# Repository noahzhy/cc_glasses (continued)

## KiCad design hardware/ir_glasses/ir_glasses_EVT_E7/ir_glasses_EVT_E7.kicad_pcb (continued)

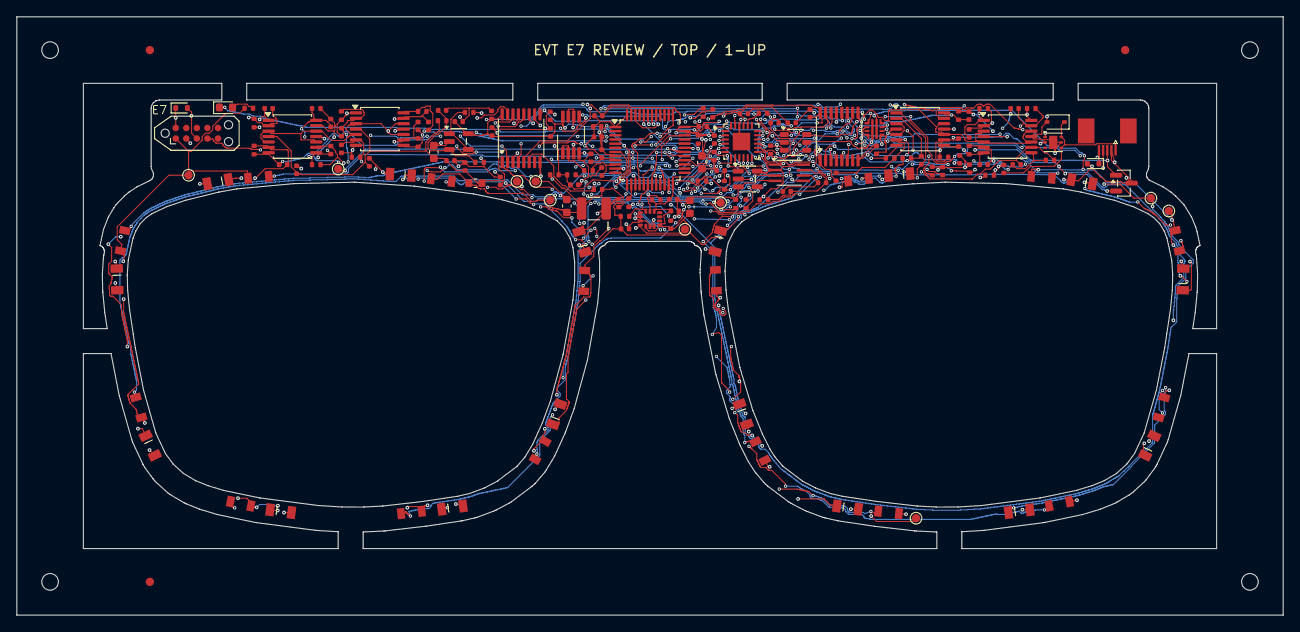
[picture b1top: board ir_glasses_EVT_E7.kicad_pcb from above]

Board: 4 copper layers, 152.3 x 72.0 mm, 171 parts (0 on the bottom side), 97 nets.

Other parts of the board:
FID1, FID2, FID3: Fiducial_1mm_Mask2mm
H1, H2, H3, H4: MountingHole_2mm

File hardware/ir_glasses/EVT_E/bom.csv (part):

Reference,Value,Footprint,Quantity,Populate,X_mm,Y_mm,Rotation_deg,Side
U9,STM32C031C6T6,IR_Glasses:LQFP-48_7x7mm_P0.5mm,1,Yes,110,63,0,front
U1,TLC59283RGER,IR_Glasses:Texas_RGE0024C_VQFN-24-1EP_4x4mm_P0.5mm_EP2.1x2.1mm,1,Yes,121,62,0,front
U10,LSM6DS3TR-C,IR_Glasses:LGA-14_3x2.5mm_P0.5mm_LayoutBorder3x4y,1,Yes,110,71.3,0,front
U6,TLV9061IDBVR,IR_Glasses:SOT-23-5,1,Yes,87,62,0,front
J1,TE 0-1734839-5,IR_Glasses:TE_0-1734839-5_1x05-1MP_P0.5mm_Horizontal,1,Yes,165,61.7,180,front
J2,TC2050-IDC-NL / ARM2010,IR_Glasses:Tag-Connect_TC2050-IDC-NL_2x05_P1.27mm_Vertical,1,PCB pads only,55.5,61,0,front
U11,PESD3V3L2BT,IR_Glasses:SOT-23,1,Yes,167.5,67.0,0,front
D17,PESD3V3S1BA,IR_Glasses:D_SOD-323,1,Yes,159.0,60.0,90,front
FB1,600R@100MHz 500mA,IR_Glasses:L_0603_1608Metric,1,Yes,89.0,67.0,0,front
NT1,AGND-GND star,IR_Glasses:NetTie-2_SMD_Pad0.5mm,1,PCB pads only,92.0,67.0,0,front
R1,2.65k,IR_Glasses:R_0402_1005Metric,1,Yes,125.75,63.25,90,front
R2,10k,IR_Glasses:R_0402_1005Metric,1,Yes,85.0,59.5,0,front
R3,10k,IR_Glasses:R_0402_1005Metric,1,Yes,86.0,64.5,0,front
R4,10k,IR_Glasses:R_0402_1005Metric,1,Yes,103.5,61.0,0,front
R5,100k,IR_Glasses:R_0402_1005Metric,1,Yes,115.8,61.0,90,front
R6,4.7k,IR_Glasses:R_0402_1005Metric,1,Yes,113.0,70.0,0,front
R7,4.7k,IR_Glasses:R_0402_1005Metric,1,Yes,113.5,72.0,90,front
R8,22,IR_Glasses:R_0402_1005Metric,1,Yes,154.0,66.0,0,front
R9,22,IR_Glasses:R_0402_1005Metric,1,Yes,170.0,69.5,0,front
R10,10k,IR_Glasses:R_0402_1005Metric,1,Yes,125.75,60.0,90,front
R11,100,IR_Glasses:R_0402_1005Metric,1,Yes,102.0,67.0,0,front
R12,100,IR_Glasses:R_0402_1005Metric,1,Yes,116.0,67.0,90,front
R13,47,IR_Glasses:R_0402_1005Metric,1,Yes,89.75,60.0,90,front
U2,TLV9064IPWR,IR_Glasses:TSSOP-14_4.4x5mm_P0.65mm,1,Yes,77.5,60.5,0,front
U3,TLV9064IPWR,IR_Glasses:TSSOP-14_4.4x5mm_P0.65mm,1,Yes,67,61.4,0,front
PD1,PD15-22B/TR8,IR_Glasses:Everlight_PD15_22B,1,Yes,99.1474,94.9322,69.734,front
D1,IR11-21C/TR8,IR_Glasses:Everlight_IR11_21C,1,Yes,97.2266,99.389,61.38,front
RF1,100k,IR_Glasses:R_0402_1005Metric,1,Yes,72.888,58.875,90,front
CF1,22p C0G,IR_Glasses:C_0402_1005Metric,1,Yes,72.888,60.875,90,front
PD2,PD15-22B/TR8,IR_Glasses:Everlight_PD15_22B,1,Yes,86.2915,106.4166,9.481,front
D2,IR11-21C/TR8,IR_Glasses:Everlight_IR11_21C,1,Yes,81.3647,107.0997,6.53,front
RF2,100k,IR_Glasses:R_0402_1005Metric,1,Yes,74.638,63.875,0,front
CF2,22p C0G,IR_Glasses:C_0402_1005Metric,1,Yes,72.888,62.875,90,front
PD3,PD15-22B/TR8,IR_Glasses:Everlight_PD15_22B,1,Yes,65.5404,106.8475,-7.387,front
D3,IR11-21C/TR8,IR_Glasses:Everlight_IR11_21C,1,Yes,60.667,106.0473,-11.779,front
RF3,100k,IR_Glasses:R_0402_1005Metric,1,Yes,82.112,62.125,90,front
CF3,22p C0G,IR_Glasses:C_0402_1005Metric,1,Yes,82.112,60.125,90,front
PD4,PD15-22B/TR8,IR_Glasses:Everlight_PD15_22B,1,Yes,49.5328,98.7372,-65.946,front
D4,IR11-21C/TR8,IR_Glasses:Everlight_IR11_21C,1,Yes,48.0093,94.1124,-74.093,front
RF4,100k,IR_Glasses:R_0402_1005Metric,1,Yes,82.612,58.375,0,front
CF4,22p C0G,IR_Glasses:C_0402_1005Metric,1,Yes,83.362,60.125,90,front
PD5,PD15-22B/TR8,IR_Glasses:Everlight_PD15_22B,1,Yes,45.494200000000006,78.5897,-89.524,front
D5,IR11-21C/TR8,IR_Glasses:Everlight_IR11_21C,1,Yes,46.0878,73.8218,-105.15,front
RF5,100k,IR_Glasses:R_0402_1005Metric,1,Yes,62.388,59.775,90,front
CF5,22p C0G,IR_Glasses:C_0402_1005Metric,1,Yes,64.138,58.025,0,front
PD6,PD15-22B/TR8,IR_Glasses:Everlight_PD15_22B,1,Yes,57.9682,66.4324,-167.812,front
D6,IR11-21C/TR8,IR_Glasses:Everlight_IR11_21C,1,Yes,62.8597,65.8002,-174.743,front
RF6,100k,IR_Glasses:R_0402_1005Metric,1,Yes,62.388,63.025,90,front
CF6,22p C0G,IR_Glasses:C_0402_1005Metric,1,Yes,65.888,64.775,0,front
PD7,PD15-22B/TR8,IR_Glasses:Everlight_PD15_22B,1,Yes,80.0574,65.60249999999999,176.212,front
D7,IR11-21C/TR8,IR_Glasses:Everlight_IR11_21C,1,Yes,84.9772,66.1358,172.509,front
RF7,100k,IR_Glasses:R_0402_1005Metric,1,Yes,69.862,64.775,0,front
CF7,22p C0G,IR_Glasses:C_0402_1005Metric,1,Yes,71.612,63.025,90,front
PD8,PD15-22B/TR8,IR_Glasses:Everlight_PD15_22B,1,Yes,102.2158,73.9515,106.619,front
D8,IR11-21C/TR8,IR_Glasses:Everlight_IR11_21C,1,Yes,102.5903,78.7863,87.338,front
RF8,100k,IR_Glasses:R_0402_1005Metric,1,Yes,69.862,58.025,0,front
CF8,22p C0G,IR_Glasses:C_0402_1005Metric,1,Yes,71.612,59.775,90,front
U7,TMUX1308PWR,IR_Glasses:TSSOP-16_4.4x5mm_P0.65mm,1,Yes,95,62,0,front
U4,TLV9064IPWR,IR_Glasses:TSSOP-14_4.4x5mm_P0.65mm,1,Yes,142.5,60.5,0,front
U5,TLV9064IPWR,IR_Glasses:TSSOP-14_4.4x5mm_P0.65mm,1,Yes,153,61.4,0,front
PD9,PD15-22B/TR8,IR_Glasses:Everlight_PD15_22B,1,Yes,120.8321,94.9333,-70.297,front
D9,IR11-21C/TR8,IR_Glasses:Everlight_IR11_21C,1,Yes,122.806,99.4398,-61.268,front
RF9,100k,IR_Glasses:R_0402_1005Metric,1,Yes,137.888,58.875,90,front
CF9,22p C0G,IR_Glasses:C_0402_1005Metric,1,Yes,137.888,60.875,90,front
PD10,PD15-22B/TR8,IR_Glasses:Everlight_PD15_22B,1,Yes,133.70850000000002,106.4166,-9.481,front
D10,IR11-21C/TR8,IR_Glasses:Everlight_IR11_21C,1,Yes,138.6353,107.0997,-6.53,front
RF10,100k,IR_Glasses:R_0402_1005Metric,1,Yes,137.888,62.875,90,front
CF10,22p C0G,IR_Glasses:C_0402_1005Metric,1,Yes,136.638,62.125,90,front
PD11,PD15-22B/TR8,IR_Glasses:Everlight_PD15_22B,1,Yes,154.4596,106.8475,7.387,front
D11,IR11-21C/TR8,IR_Glasses:Everlight_IR11_21C,1,Yes,159.333,106.0473,11.779,front
RF11,100k,IR_Glasses:R_0402_1005Metric,1,Yes,145.362,63.875,0,front
CF11,22p C0G,IR_Glasses:C_0402_1005Metric,1,Yes,147.112,62.125,90,front
PD12,PD15-22B/TR8,IR_Glasses:Everlight_PD15_22B,1,Yes,170.4672,98.7372,65.946,front
D12,IR11-21C/TR8,IR_Glasses:Everlight_IR11_21C,1,Yes,171.9907,94.1124,74.093,front
RF12,100k,IR_Glasses:R_0402_1005Metric,1,Yes,147.112,58.875,90,front
CF12,22p C0G,IR_Glasses:C_0402_1005Metric,1,Yes,148.362,58.875,90,front
PD13,PD15-22B/TR8,IR_Glasses:Everlight_PD15_22B,1,Yes,174.5058,78.5897,89.524,front
D13,IR11-21C/TR8,IR_Glasses:Everlight_IR11_21C,1,Yes,173.91219999999998,73.8218,105.15,front
RF13,100k,IR_Glasses:R_0402_1005Metric,1,Yes,150.138,58.025,0,front
CF13,22p C0G,IR_Glasses:C_0402_1005Metric,1,Yes,148.388,61.025,90,front
PD14,PD15-22B/TR8,IR_Glasses:Everlight_PD15_22B,1,Yes,162.0318,66.4324,167.812,front
D14,IR11-21C/TR8,IR_Glasses:Everlight_IR11_21C,1,Yes,157.1403,65.8002,174.743,front
RF14,100k,IR_Glasses:R_0402_1005Metric,1,Yes,148.388,63.025,90,front
CF14,22p C0G,IR_Glasses:C_0402_1005Metric,1,Yes,150.138,64.775,0,front
PD15,PD15-22B/TR8,IR_Glasses:Everlight_PD15_22B,1,Yes,139.9583,65.5798,-174.859,front
D15,IR11-21C/TR8,IR_Glasses:Everlight_IR11_21C,1,Yes,135.00979999999998,66.0825,-173.002,front
RF15,100k,IR_Glasses:R_0402_1005Metric,1,Yes,158.112,64.025,0,front
CF15,22p C0G,IR_Glasses:C_0402_1005Metric,1,Yes,154.112,64.775,0,front
PD16,PD15-22B/TR8,IR_Glasses:Everlight_PD15_22B,1,Yes,117.7834,73.8917,-106.197,front
D16,IR11-21C/TR8,IR_Glasses:Everlight_IR11_21C,1,Yes,117.4309,78.7127,-87.24,front
RF16,100k,IR_Glasses:R_0402_1005Metric,1,Yes,155.862,58.025,0,front
CF16,22p C0G,IR_Glasses:C_0402_1005Metric,1,Yes,153.862,58.025,0,front
U8,TMUX1308PWR,IR_Glasses:TSSOP-16_4.4x5mm_P0.65mm,1,Yes,131,61.5,0,front
C1,1u,IR_Glasses:C_0402_1005Metric,1,Yes,85.0,58.25,0,front
C2,100n,IR_Glasses:C_0402_1005Metric,1,Yes,121.25,58.562,0,front
C3,100n,IR_Glasses:C_0402_1005Metric,1,Yes,76.388,64.5,90,front
C4,100n,IR_Glasses:C_0402_1005Metric,1,Yes,61.888,58.15,0,front
C5,100n,IR_Glasses:C_0402_1005Metric,1,Yes,136.638,60.0,90,front
C6,100n,IR_Glasses:C_0402_1005Metric,1,Yes,147.888,64.65,0,front
C7,100n,IR_Glasses:C_0402_1005Metric,1,Yes,88.138,59.55,0,front
C8,100n,IR_Glasses:C_0402_1005Metric,1,Yes,97.862,58.475,0,front
C9,100n,IR_Glasses:C_0402_1005Metric,1,Yes,133.862,57.975,0,front
C10,100n,IR_Glasses:C_0402_1005Metric,1,Yes,112.75,68.913,0,front
C11,100n,IR_Glasses:C_0402_1005Metric,1,Yes,104.088,64.25,90,front
C12,100n,IR_Glasses:C_0402_1005Metric,1,Yes,112.412,72.05,90,front
C13,100n,IR_Glasses:C_0402_1005Metric,1,Yes,107.5,72.212,90,front
C14,100n,IR_Glasses:C_0402_1005Metric,1,Yes,170.5,68.05,0,front
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
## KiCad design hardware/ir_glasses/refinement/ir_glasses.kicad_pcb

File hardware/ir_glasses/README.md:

# IR Glasses EVT E6

当前修复后的设计为 **EVT E6 P3**：每颗 IR LED 同步读取相邻两个 PD，16 组固定配对。E4 原工程、原 BOM 和生产包保留。

- [E6 工程及交付说明](ir_glasses_EVT_E6/README.md)
- [P3 运放替代与模拟验证](ir_glasses_EVT_E6/analog_validation_report.md)
- [P2 完善与复核报告](ir_glasses_EVT_E6/production_refinement_report.md)
- [P1 历史修复记录](ir_glasses_EVT_E6/production_fix_report.md)
- [完整 E6 工程包](ir_glasses_EVT_E6.zip)
- [载框 Gerber 上传包](ir_glasses_EVT_E6_JLC_upload.zip)
- [贴片交付包](ir_glasses_EVT_E6/EVT_E6_SMT_handoff.zip)
- [贴好片示意图](ir_glasses_EVT_E6/populated_assembly.pdf)
- [E6 BOM](ir_glasses_EVT_E6/bom_EVT_E6.xlsx)

主板及载框 DRC、ERC、原理图一致性、CAM/BOM/CPL 静态检查已通过。正常输入要求 3.3V±3%，板上新增持续限流和过压恢复保护。工厂 DFM、备料、实际排线和首板电气/光学/固件验证仍待完成；本包不含可烧录固件，不能把静态检查视为量产实测放行。

## E4 基线与历史证据

- [E4 KiCad 工程](ir_glasses_EVT_E4/ir_glasses_EVT_E4.kicad_pro)
- [E4 完整交付包](ir_glasses_EVT_E4.zip)
- [E4 上传包](ir_glasses_EVT_E4_JLC_upload.zip)
- [E4 BOM](ir_glasses_EVT_E4/material_freeze/bom.xlsx)
- [本次修复前复核记录](EVT_E6_preproduction_audit/REVIEW.md)

E6 BOM 以两板净用量作参考，不含贴片损耗、最小起订量及备件；实际生产数量另行确定。

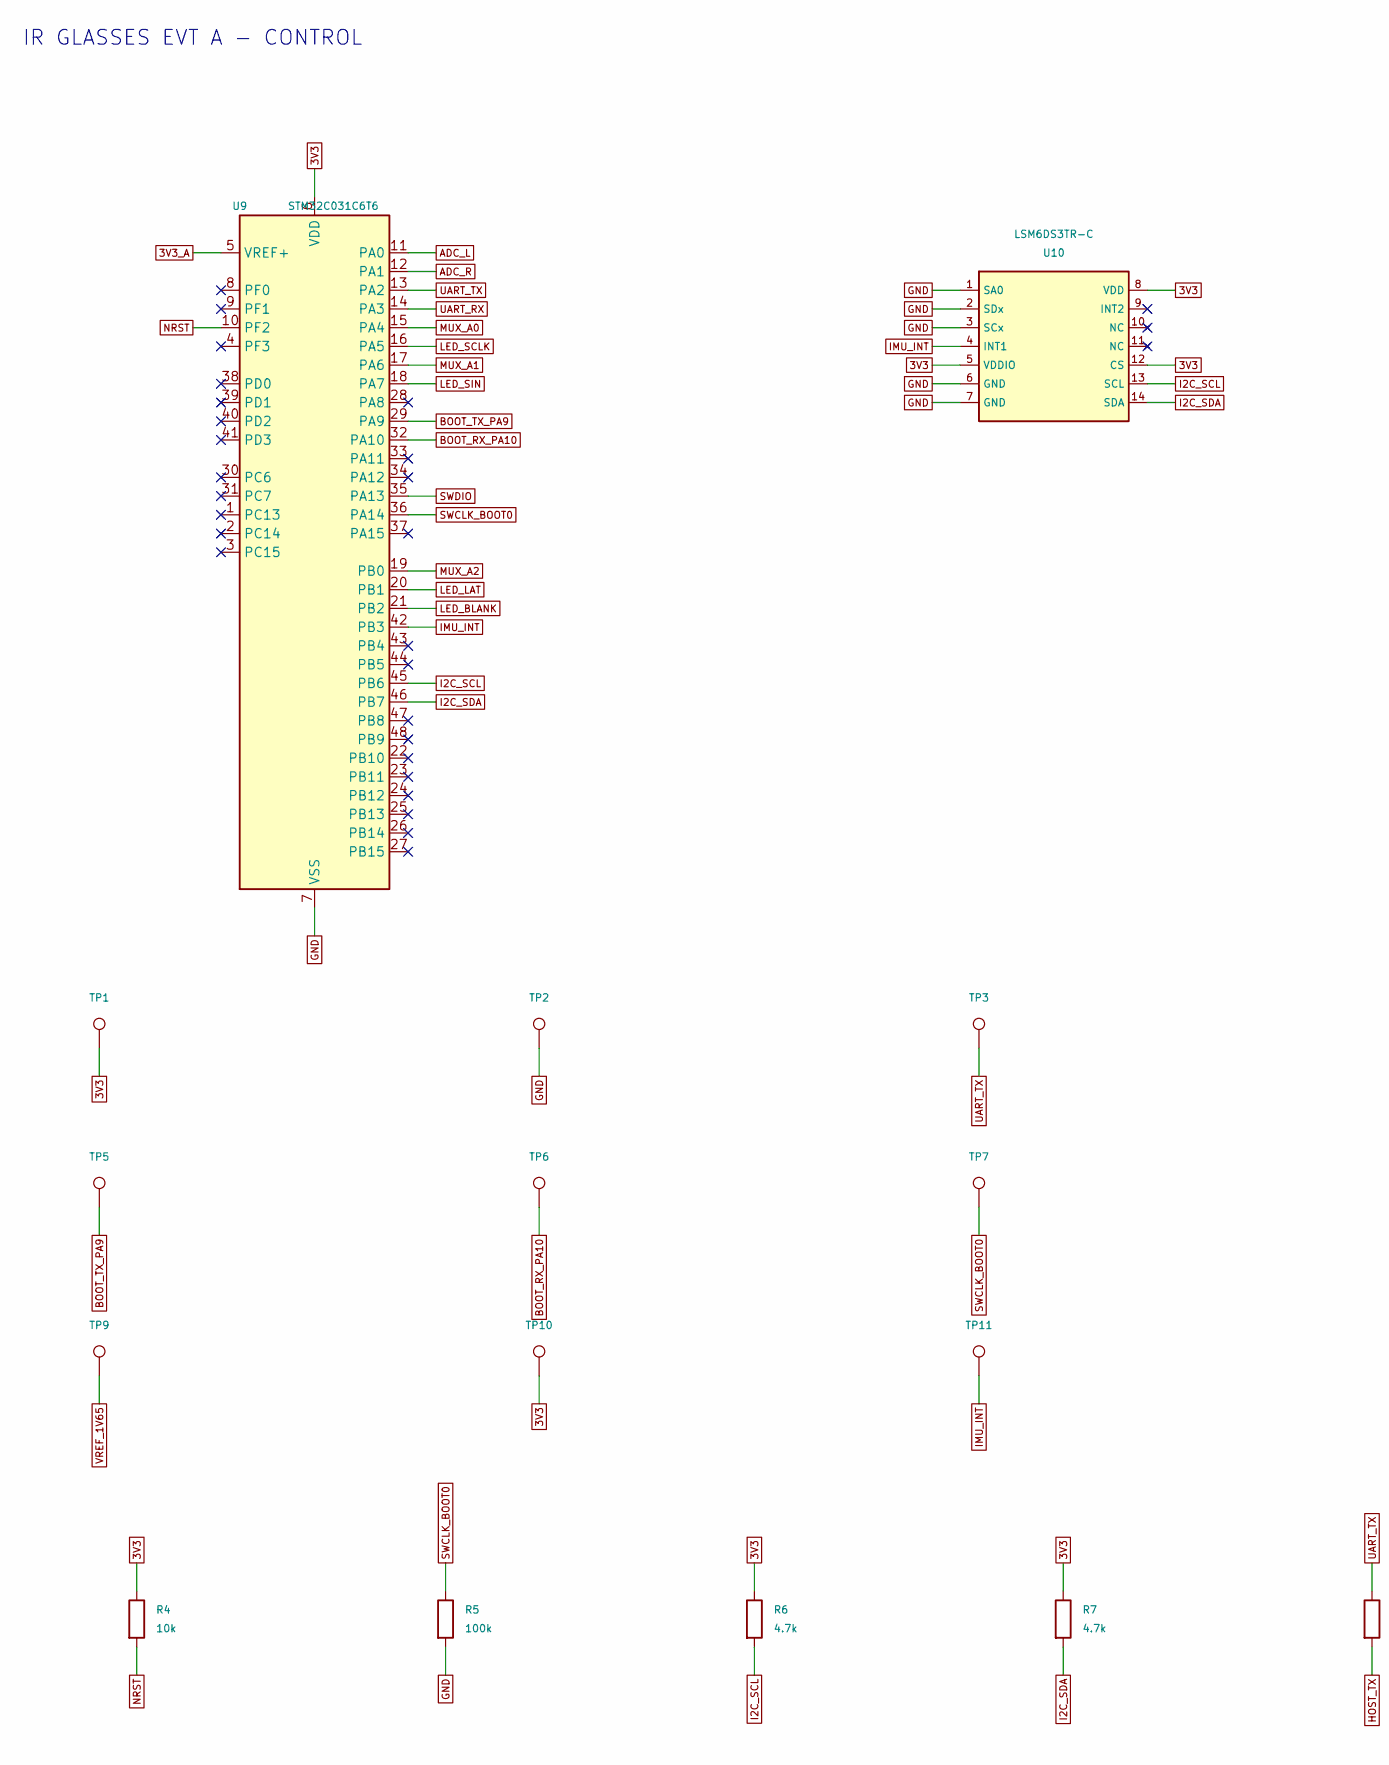
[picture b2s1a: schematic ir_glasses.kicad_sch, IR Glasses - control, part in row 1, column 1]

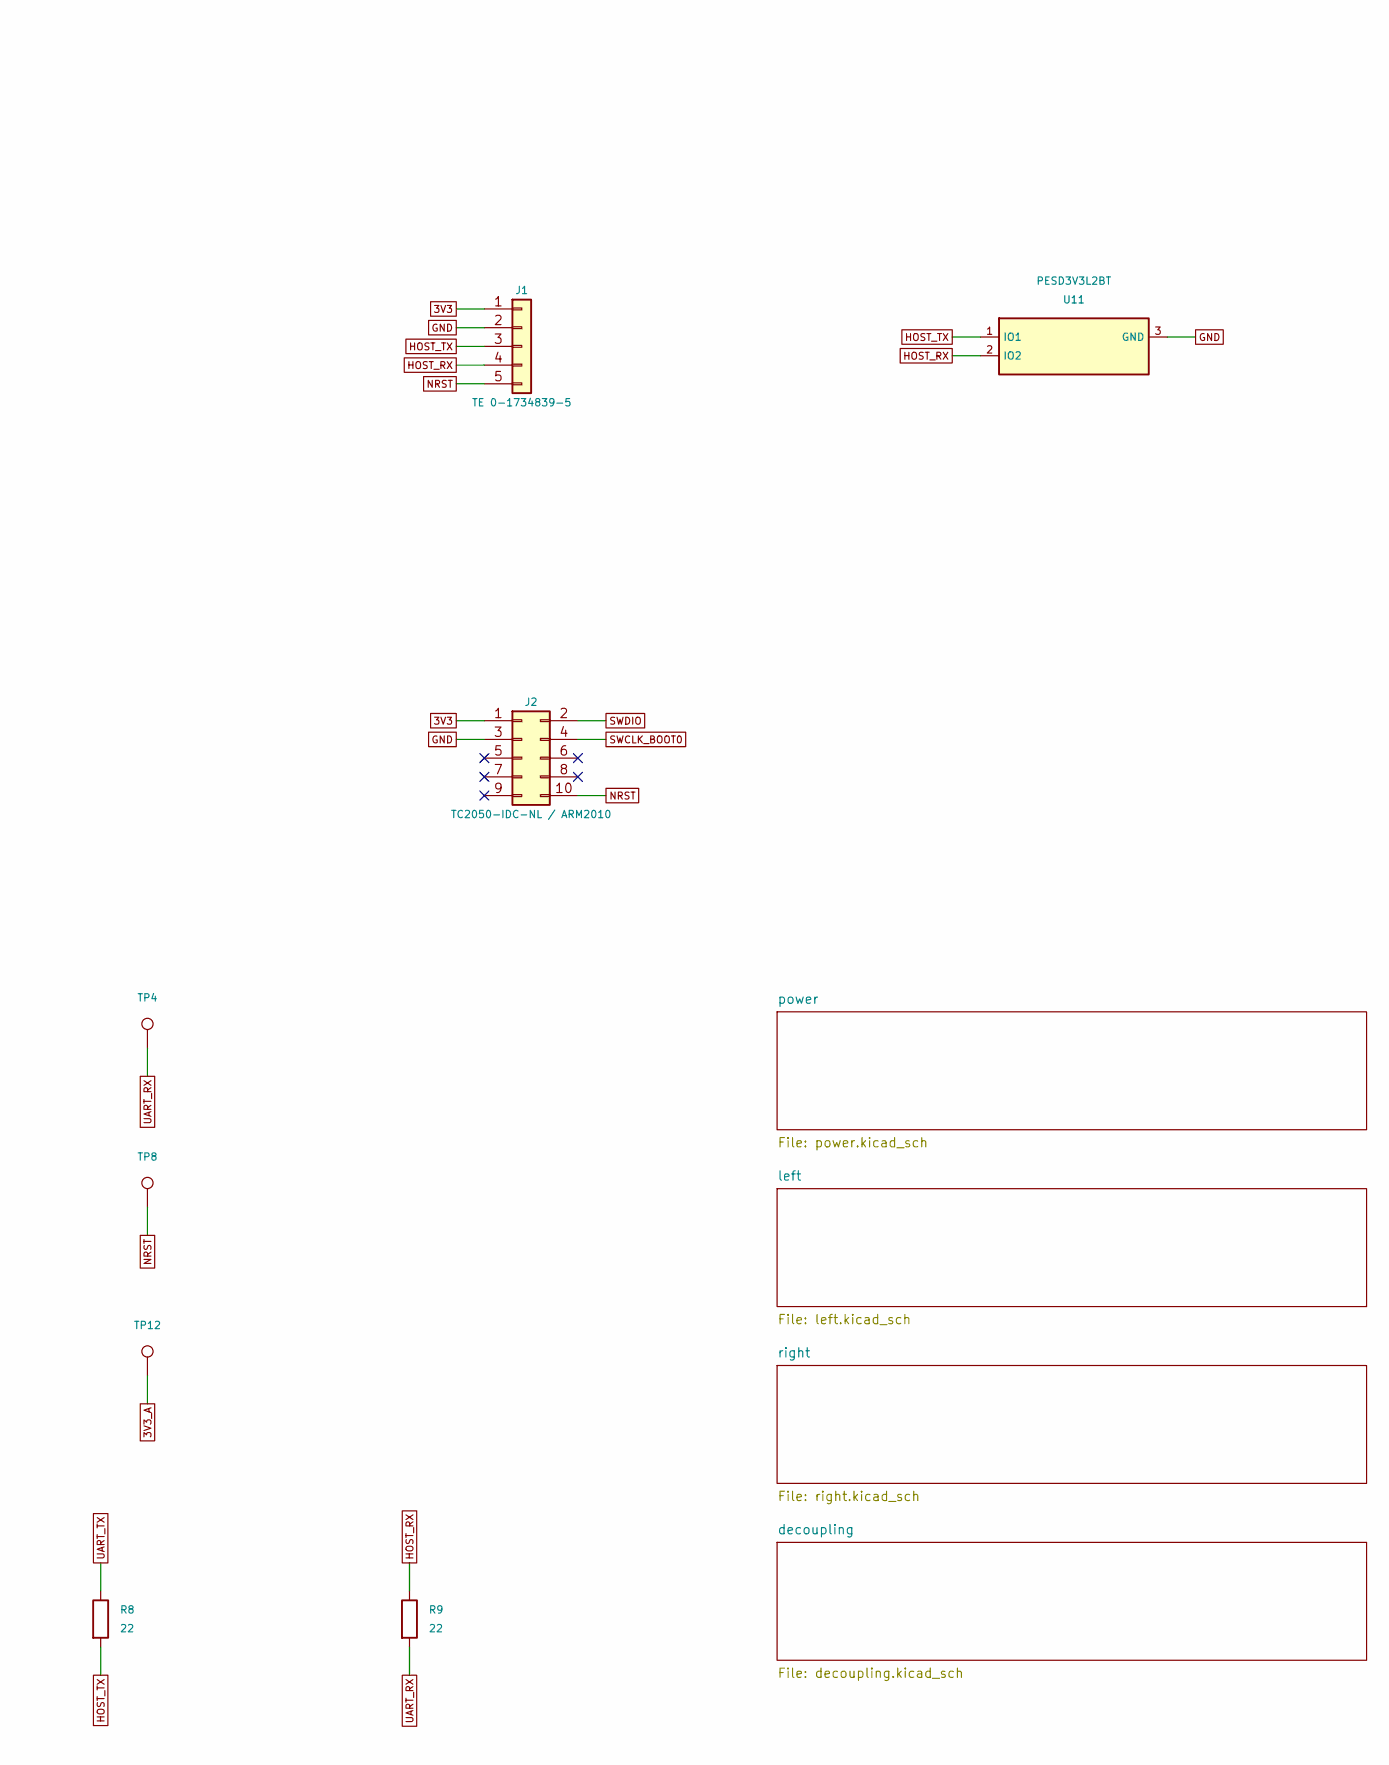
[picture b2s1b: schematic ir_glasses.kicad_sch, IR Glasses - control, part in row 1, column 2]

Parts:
J1: TE 0-1734839-5; TE_0-1734839-5_1x05-1MP_P0.5mm_Horizontal
J2: TC2050-IDC-NL / ARM2010; Tag-Connect_TC2050-IDC-NL_2x05_P1.27mm_Vertical
R4: 10k; R_0402_1005Metric
R5: 100k; R_0402_1005Metric
R6, R7: 4.7k; R_0402_1005Metric
R8, R9: 22; R_0402_1005Metric
TP1, TP10: 3V3; TestPoint_Pad_D1.0mm
TP2: GND; TestPoint_Pad_D1.0mm
TP3: UART_TX; TestPoint_Pad_D1.0mm
TP4: UART_RX; TestPoint_Pad_D1.0mm
TP5: BOOT_TX_PA9; TestPoint_Pad_D1.0mm
TP6: BOOT_RX_PA10; TestPoint_Pad_D1.0mm
TP7: SWCLK_BOOT0; TestPoint_Pad_D1.0mm
TP8: NRST; TestPoint_Pad_D1.0mm
TP9: VREF_1V65; TestPoint_Pad_D1.0mm
TP11: IMU_INT; TestPoint_Pad_D1.0mm
TP12: 3V3_A; TestPoint_Pad_D1.0mm
U9: STM32C031C6T6; LQFP-48_7x7mm_P0.5mm
U10: LSM6DS3TR-C; LGA-14_3x2.5mm_P0.5mm_LayoutBorder3x4y
U11: PESD3V3L2BT; SOT-23

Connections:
3V3: J1.1, J2.1, R4.1, R6.1, R7.1, TP1.1, TP10.1, U9.6 (VDD), U10.5 (VDDIO), U10.8 (VDD), U10.12 (CS); also elsewhere on the board
3V3_A: TP12.1, U9.5 (VREF+); also elsewhere on the board
ADC_L: U9.11 (PA0); also elsewhere on the board
ADC_R: U9.12 (PA1); also elsewhere on the board
BOOT_RX_PA10: TP6.1, U9.32 (PA10)
BOOT_TX_PA9: TP5.1, U9.29 (PA9)
GND: J1.2, J2.3, R5.2, TP2.1, U9.7 (VSS), U10.1 (SA0), U10.2 (SDx), U10.3 (SCx), U10.6 (GND), U10.7 (GND), U11.3 (GND); also elsewhere on the board
HOST_RX: J1.4, R9.1, U11.2 (IO2)
HOST_TX: J1.3, R8.2, U11.1 (IO1)
I2C_SCL: R6.2, U9.45 (PB6), U10.13 (SCL)
I2C_SDA: R7.2, U9.46 (PB7), U10.14 (SDA)
IMU_INT: TP11.1, U9.42 (PB3), U10.4 (INT1)
LED_BLANK: U9.21 (PB2); also elsewhere on the board
LED_LAT: U9.20 (PB1); also elsewhere on the board
LED_SCLK: U9.16 (PA5); also elsewhere on the board
LED_SIN: U9.18 (PA7); also elsewhere on the board
MUX_A0: U9.15 (PA4); also elsewhere on the board
MUX_A1: U9.17 (PA6); also elsewhere on the board
MUX_A2: U9.19 (PB0); also elsewhere on the board
NRST: J1.5, J2.10, R4.2, TP8.1, U9.10 (PF2)
SWCLK_BOOT0: J2.4, R5.1, TP7.1, U9.36 (PA14)
SWDIO: J2.2, U9.35 (PA13)
UART_RX: R9.2, TP4.1, U9.14 (PA3)
UART_TX: R8.1, TP3.1, U9.13 (PA2)
VREF_1V65: TP9.1; also elsewhere on the board

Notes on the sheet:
IR GLASSES EVT A - CONTROL

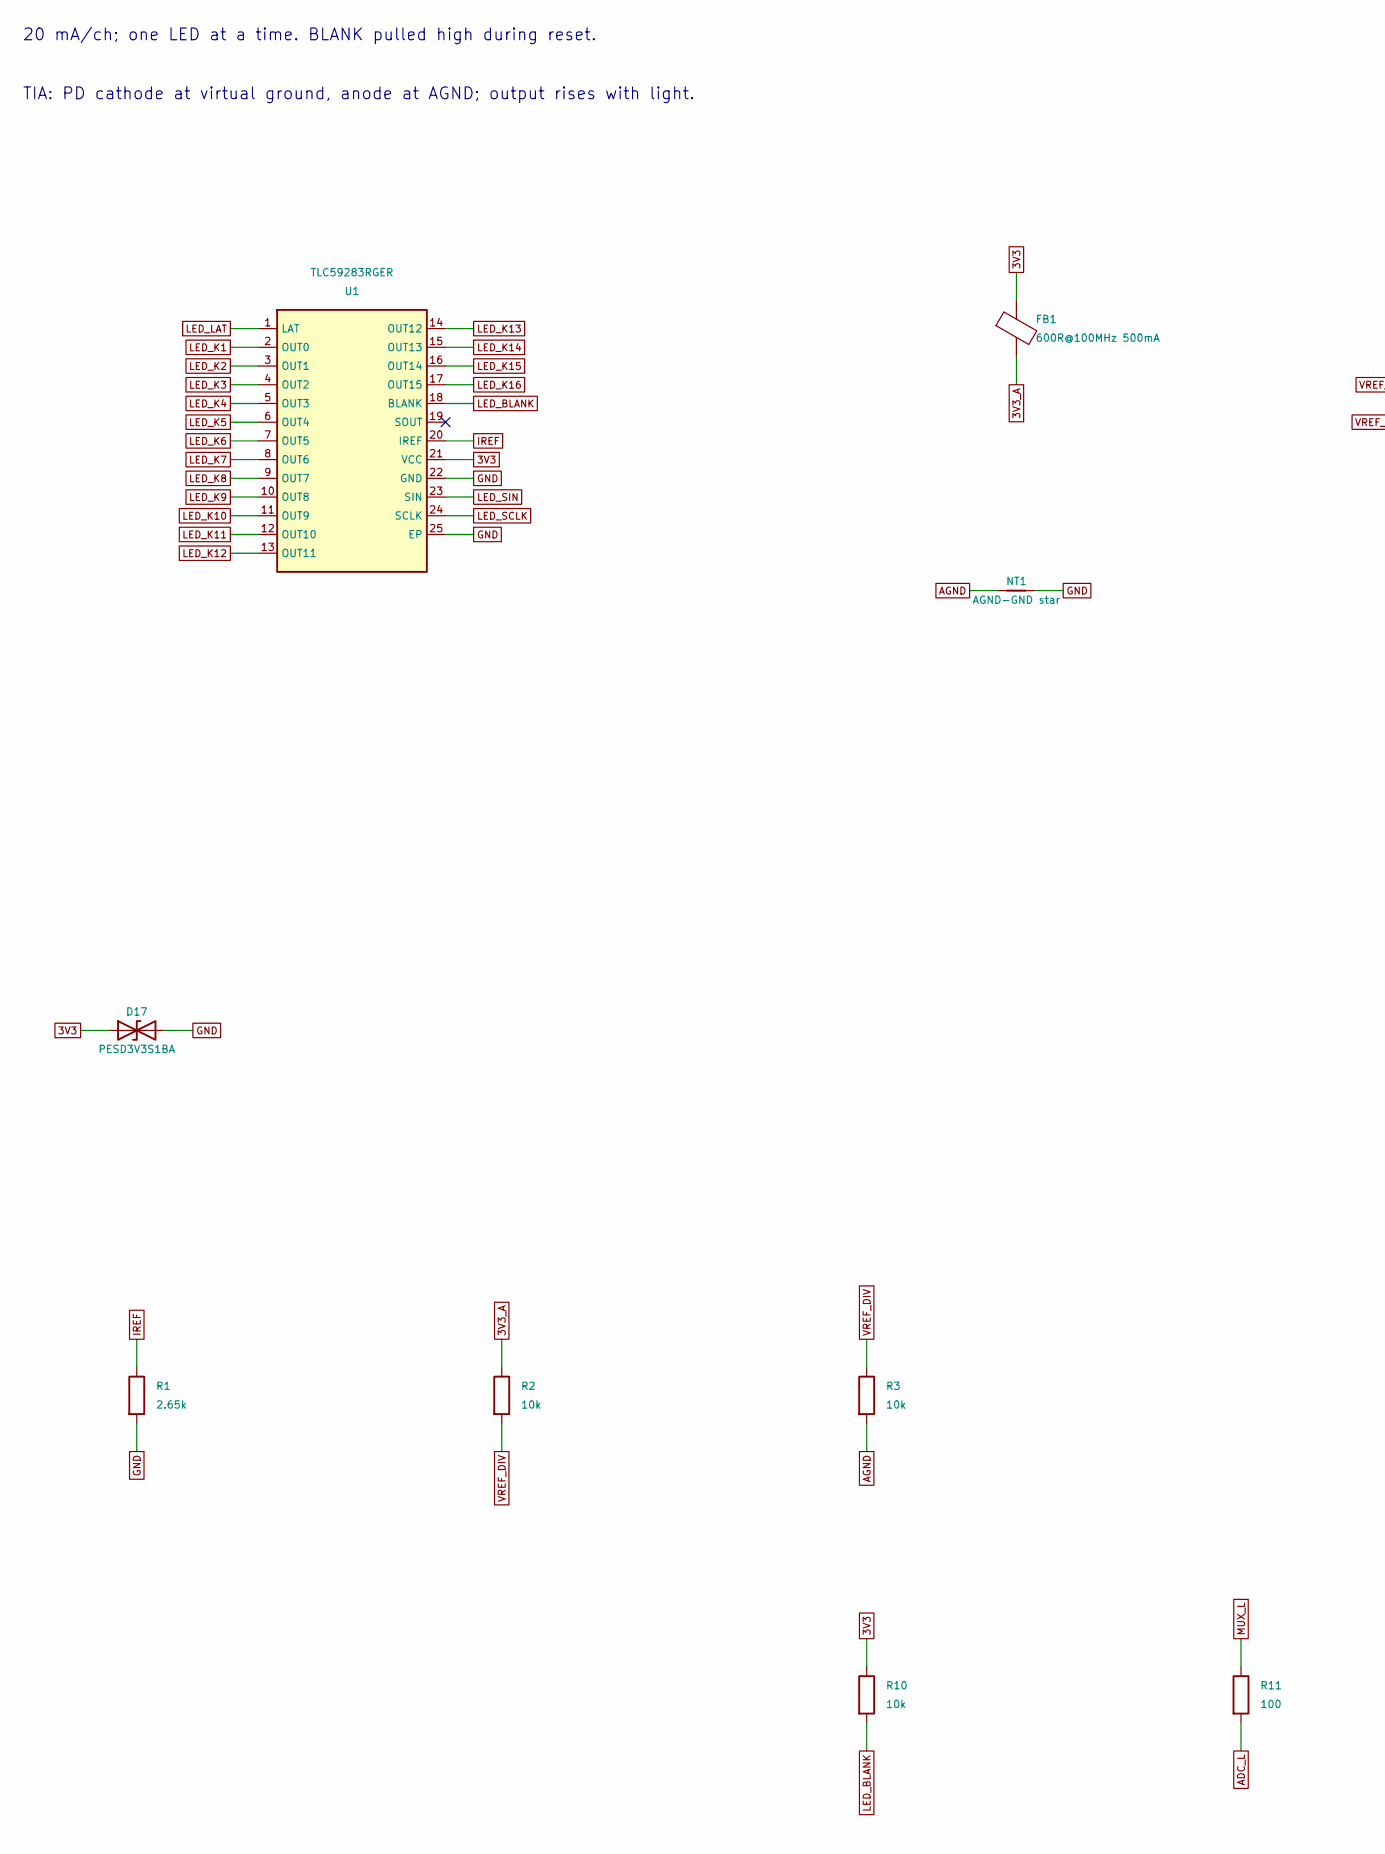
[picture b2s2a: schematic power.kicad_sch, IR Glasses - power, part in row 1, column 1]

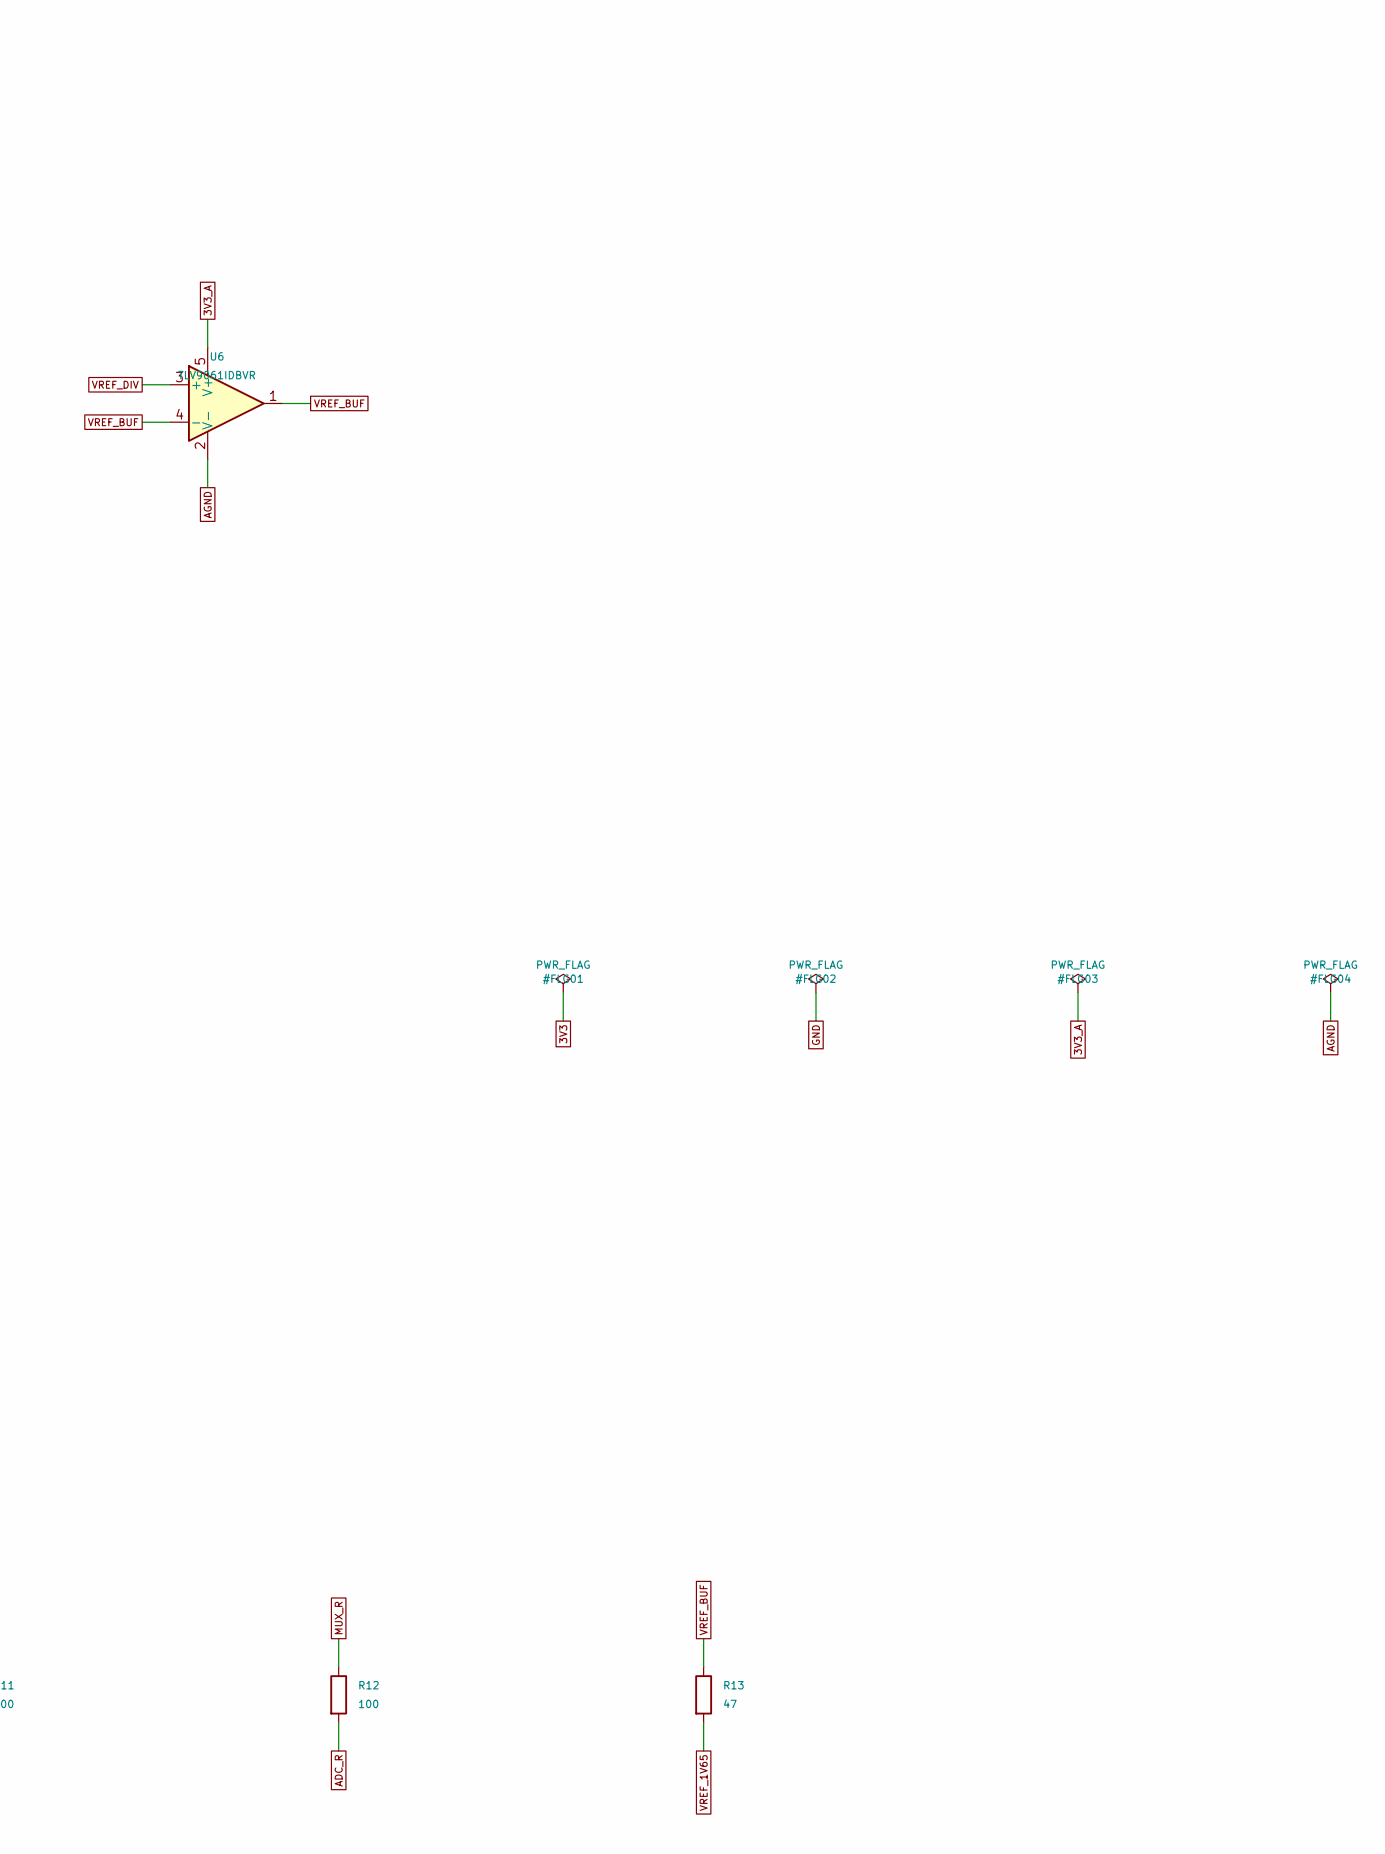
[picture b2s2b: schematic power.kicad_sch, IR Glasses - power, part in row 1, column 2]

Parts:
D17: PESD3V3S1BA; D_SOD-323
FB1: 600R@100MHz 500mA; L_0603_1608Metric
NT1: AGND-GND star; NetTie-2_SMD_Pad0.5mm
R1: 2.65k; R_0402_1005Metric
R2, R3, R10: 10k; R_0402_1005Metric
R11, R12: 100; R_0402_1005Metric
R13: 47; R_0402_1005Metric
U1: TLC59283RGER; Texas_RGE0024C_VQFN-24-1EP_4x4mm_P0.5mm_EP2.1x2.1mm
U6: TLV9061IDBVR; SOT-23-5

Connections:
3V3: D17.1 (A1), FB1.1, R10.1, U1.21 (VCC); also elsewhere on the board
3V3_A: FB1.2, R2.1, U6.5 (V+); also elsewhere on the board
ADC_L: R11.2; also elsewhere on the board
ADC_R: R12.2; also elsewhere on the board
AGND: NT1.1, R3.2, U6.2 (V-); also elsewhere on the board
GND: D17.2 (A2), NT1.2, R1.2, U1.22 (GND), U1.25 (EP); also elsewhere on the board
IREF: R1.1, U1.20 (IREF)
LED_BLANK: R10.2, U1.18 (BLANK); also elsewhere on the board
LED_K1: U1.2 (OUT0); also elsewhere on the board
LED_K2: U1.3 (OUT1); also elsewhere on the board
LED_K3: U1.4 (OUT2); also elsewhere on the board
LED_K4: U1.5 (OUT3); also elsewhere on the board
LED_K5: U1.6 (OUT4); also elsewhere on the board
LED_K6: U1.7 (OUT5); also elsewhere on the board
LED_K7: U1.8 (OUT6); also elsewhere on the board
LED_K8: U1.9 (OUT7); also elsewhere on the board
LED_K9: U1.10 (OUT8); also elsewhere on the board
LED_K10: U1.11 (OUT9); also elsewhere on the board
LED_K11: U1.12 (OUT10); also elsewhere on the board
LED_K12: U1.13 (OUT11); also elsewhere on the board
LED_K13: U1.14 (OUT12); also elsewhere on the board
LED_K14: U1.15 (OUT13); also elsewhere on the board
LED_K15: U1.16 (OUT14); also elsewhere on the board
LED_K16: U1.17 (OUT15); also elsewhere on the board
LED_LAT: U1.1 (LAT); also elsewhere on the board
LED_SCLK: U1.24 (SCLK); also elsewhere on the board
LED_SIN: U1.23 (SIN); also elsewhere on the board
MUX_L: R11.1; also elsewhere on the board
MUX_R: R12.1; also elsewhere on the board
VREF_1V65: R13.2; also elsewhere on the board
VREF_BUF: R13.1, U6.1, U6.4 (-)
VREF_DIV: R2.2, R3.1, U6.3 (+); also elsewhere on the board

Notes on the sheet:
20 mA/ch; one LED at a time. BLANK pulled high during reset.
TIA: PD cathode at virtual ground, anode at AGND; output rises with light.
